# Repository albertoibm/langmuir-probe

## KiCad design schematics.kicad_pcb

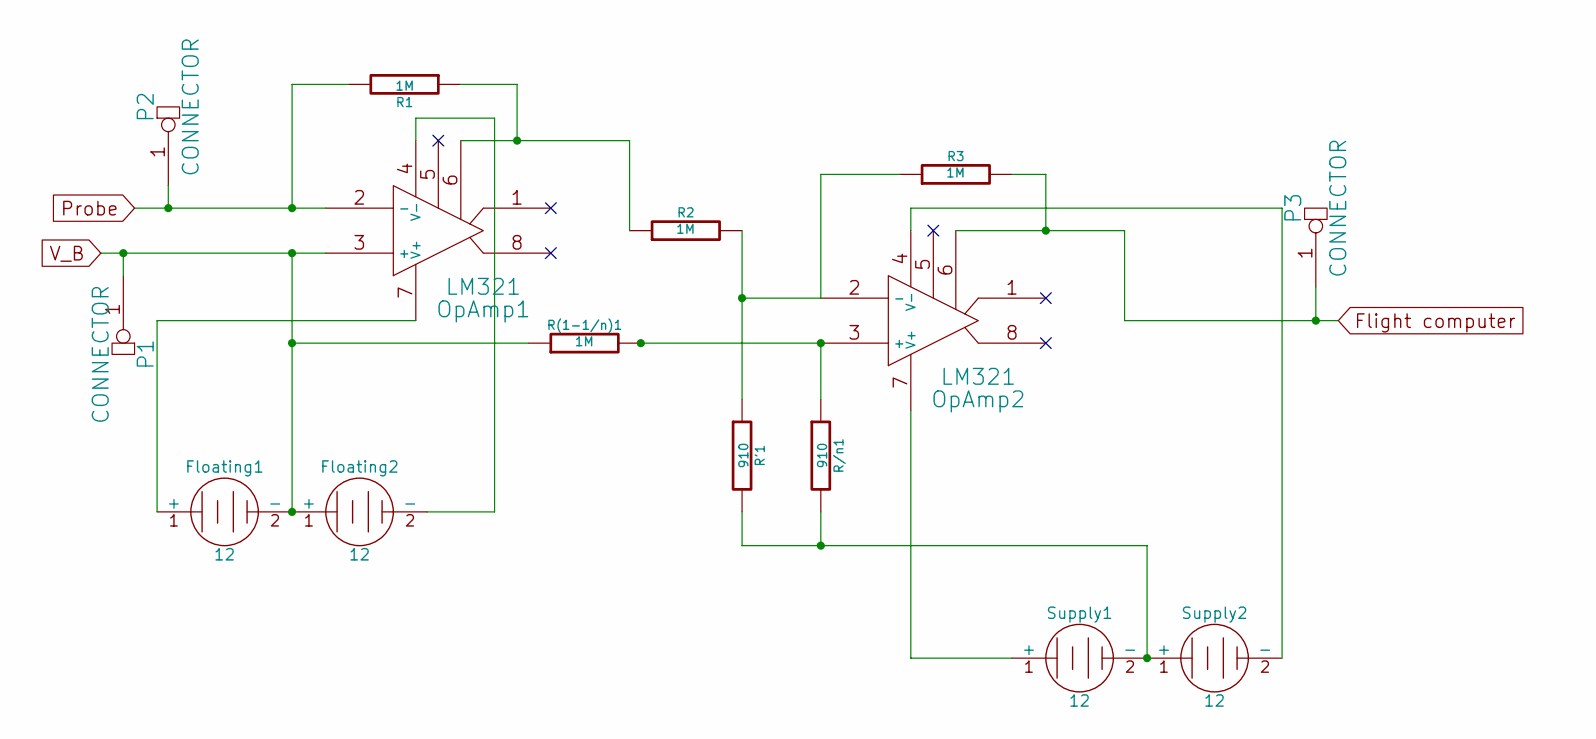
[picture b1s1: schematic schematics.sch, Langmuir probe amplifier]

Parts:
Floating1, Floating2: 12
OpAmp1, OpAmp2: LM321
P1, P2, P3: CONNECTOR
R1, R2, R3: 1M
R'1: 910
R(1-1/n)1: 1M
R/n1: 910
Supply1, Supply2: 12

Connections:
Flight computer: OpAmp2.6, P3.1, R3.2
unnamed: OpAmp2.3 (+), R(1-1/n)1.2, R/n1.1
unnamed: OpAmp2.4 (V-), Supply2.2 (-)
unnamed: OpAmp2.2 (-), R2.2, R3.1, R'1.1
unnamed: OpAmp2.7 (V+), Supply1.1 (+)
unnamed: OpAmp1.6, R1.1, R2.1
unnamed: Floating2.2 (-), OpAmp1.4 (V-)
unnamed: Floating1.1 (+), OpAmp1.7 (V+)
unnamed: R'1.2, R/n1.2, Supply1.2 (-), Supply2.1 (+)
Probe: OpAmp1.2 (-), P2.1, R1.2
V_B: Floating1.2 (-), Floating2.1 (+), OpAmp1.3 (+), P1.1, R(1-1/n)1.1

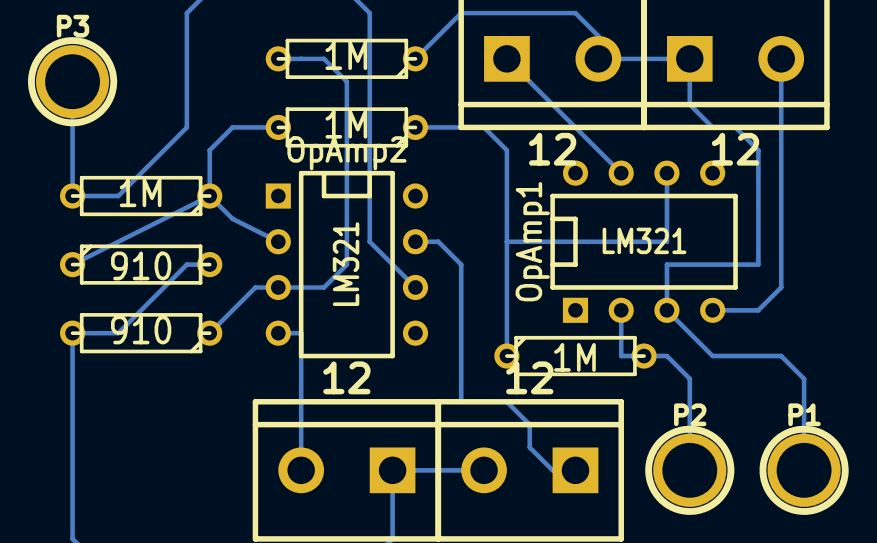
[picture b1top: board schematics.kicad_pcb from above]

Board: 2 copper layers, 15 parts (0 on the bottom side), 11 nets.

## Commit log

2015-11-09 Updated solution.pdf
